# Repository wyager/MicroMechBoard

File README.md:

# MicroMechBoard
This project is the teensy code for Will Yager's custom mechanical keyboard
project. ([blog post](http://yager.io/keyboard/keyboard.html))

The code serves two functions:

1. If plugged into USB, the device will act as a stand-alone keyboard with 33
keys. ("The master")
2. If a second device is plugged into that first device, the two devices will
share relevant information over I2C. In this way, two of these devices can be
connected to form a 66-key keyboard. With some modification to the firmware and
the I2C pull-up resistors, one could theoretically chain up to 129 boards
together (I believe).

## Building/installing
1. Install `avr-gcc`.
2. Install Teensy loader.
3. `cd src`
4. `make`
5. Drag `main.hex` into Teensy loader.
6. Program Teensy.

## Modifying key layout
1. Modify `keys[]` in `KeyMapper.cpp`.
2. Replace values like `KEY_A` with other values from `keylayouts.h`.

This should be fairly simple to figure out. Within the file, I have `keys[]`
laid out just like the physical keys.

## Program structure

### main.cpp

```
       Start USB/I2C
       Determine master/slave status
       
       forever:
              led_status
              => get hardware state from HardwareController
              => debounce buttons with ButtonDebouncer
              => detect changes in buttons with ButtonDeltaDetector
              => map button changes to key changes with KeyMapper
              =: key_changes

              led_status
              => update the slave (if it exists) with the SlaveNotifier
              =: slave_key_changes

              key_changes, slave_key_changes
              => notify the master (over USB or I2C) of key changes with the MasterNotifier
              =: led_status

```

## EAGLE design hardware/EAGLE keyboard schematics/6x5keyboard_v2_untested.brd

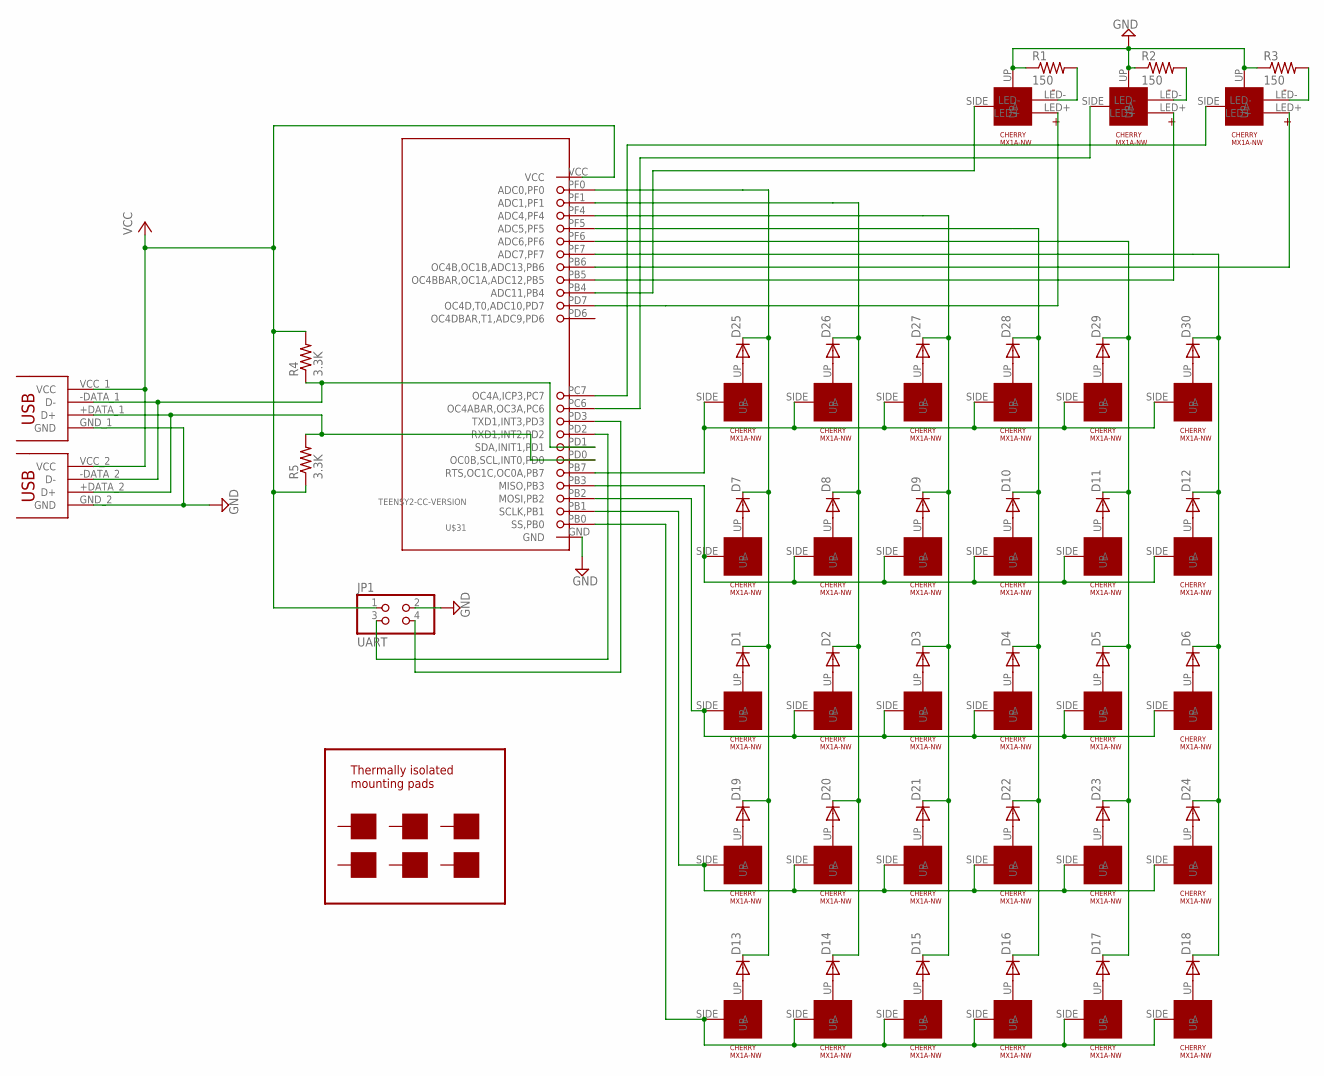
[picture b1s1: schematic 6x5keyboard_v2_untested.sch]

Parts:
D1, D2, D3, D4, D5, D6, D7, D8, D9, D10, D11, D12, D13, D14, D15, D16, D17, D18, D19, D20, D21, D22, D23, D24, D25, D26, D27, D28, D29, D30: 1N4148DO35-7; DO35-7
JP1: UART; 2X02
R1, R2, R3: 150; 0207/10
R4, R5: 3.3K; 0207/10
U$1, U$2, U$3, U$4, U$5, U$6, U$7, U$8, U$9, U$10, U$11, U$12, U$13, U$14, U$15, U$16, U$17, U$18, U$19, U$20, U$21, U$22, U$23, U$24, U$25, U$26, U$27, U$28, U$29, U$30: CHERRY-MX1A-E1NW; CHERRYMX-NN
U$31: TEENSY2-CC-VERSION; TEENSY2
U$32, U$33, U$34: CHERRY-MX1A-E1NW-LED; CHERRYMX-NN-LED
U$35: DUAL-USB-A
U$36, U$37, U$38, U$39, U$40, U$41: MOUNTING-PAD

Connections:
GND: JP1.2, R1.1, R2.1, R3.1, U$31.GND, U$32.UP, U$33.UP, U$34.UP, U$35.GND_1 (GND), U$35.GND_2 (GND)
unnamed: D1.A, U$2.UP
unnamed: D2.A, U$1.UP
unnamed: D3.A, U$3.UP
unnamed: D4.A, U$4.UP
unnamed: D5.A, U$5.UP
unnamed: D6.A, U$6.UP
unnamed: D7.A, U$7.UP
unnamed: D8.A, U$8.UP
unnamed: D9.A, U$9.UP
unnamed: D10.A, U$10.UP
unnamed: D11.A, U$11.UP
unnamed: D12.A, U$12.UP
unnamed: D13.A, U$13.UP
unnamed: D14.A, U$14.UP
unnamed: D15.A, U$15.UP
unnamed: D16.A, U$16.UP
unnamed: D17.A, U$17.UP
unnamed: D18.A, U$18.UP
unnamed: D19.A, U$19.UP
unnamed: D20.A, U$20.UP
unnamed: D21.A, U$21.UP
unnamed: D22.A, U$22.UP
unnamed: D23.A, U$23.UP
unnamed: D24.A, U$24.UP
unnamed: D25.A, U$25.UP
unnamed: D26.A, U$26.UP
unnamed: D27.A, U$27.UP
unnamed: D28.A, U$28.UP
unnamed: D29.A, U$29.UP
unnamed: D30.A, U$30.UP
unnamed: D1.C, D7.C, D13.C, D19.C, D25.C, U$31.PF0 (ADC0,PF0)
unnamed: D2.C, D8.C, D14.C, D20.C, D26.C, U$31.PF1 (ADC1,PF1)
unnamed: D3.C, D9.C, D15.C, D21.C, D27.C, U$31.PF4 (ADC4,PF4)
unnamed: D4.C, D10.C, D16.C, D22.C, D28.C, U$31.PF5 (ADC5,PF5)
unnamed: D5.C, D11.C, D17.C, D23.C, D29.C, U$31.PF6 (ADC6,PF6)
unnamed: D6.C, D12.C, D18.C, D24.C, D30.C, U$31.PF7 (ADC7,PF7)
unnamed: U$19.SIDE (A), U$20.SIDE (A), U$21.SIDE (A), U$22.SIDE (A), U$23.SIDE (A), U$24.SIDE (A), U$31.PB1 (SCLK,PB1)
unnamed: U$1.SIDE (A), U$2.SIDE (A), U$3.SIDE (A), U$4.SIDE (A), U$5.SIDE (A), U$6.SIDE (A), U$31.PB2 (MOSI,PB2)
unnamed: U$7.SIDE (A), U$8.SIDE (A), U$9.SIDE (A), U$10.SIDE (A), U$11.SIDE (A), U$12.SIDE (A), U$31.PB3 (MISO,PB3)
unnamed: U$25.SIDE (A), U$26.SIDE (A), U$27.SIDE (A), U$28.SIDE (A), U$29.SIDE (A), U$30.SIDE (A), U$31.PB7 (RTS,OC1C,OC0A,PB7)
unnamed: U$13.SIDE (A), U$14.SIDE (A), U$15.SIDE (A), U$16.SIDE (A), U$17.SIDE (A), U$18.SIDE (A), U$31.PB0 (SS,PB0)
unnamed: R1.2, U$32.LED-
unnamed: R2.2, U$33.LED-
unnamed: R3.2, U$34.LED-
unnamed: JP1.3, U$31.PD2 (RXD1,INT2,PD2)
unnamed: U$31.PB5 (OC4BBAR,OC1A,ADC12,PB5), U$33.LED+
unnamed: U$31.PB6 (OC4B,OC1B,ADC13,PB6), U$34.LED+
unnamed: U$31.PB4 (ADC11,PB4), U$32.SIDE (A)
unnamed: U$31.PC6 (OC4ABAR,OC3A,PC6), U$33.SIDE (A)
unnamed: U$31.PC7 (OC4A,ICP3,PC7), U$34.SIDE (A)
unnamed: U$31.PD7 (OC4D,T0,ADC10,PD7), U$32.LED+
unnamed: JP1.4, U$31.PD3 (TXD1,INT3,PD3)
unnamed: R4.1, U$31.PD1 (SDA,INIT1,PD1), U$35.-DATA_1 (D-), U$35.-DATA_2 (D-)
unnamed: R5.2, U$31.PD0 (OC0B,SCL,INT0,PD0), U$35.+DATA_1 (D+), U$35.+DATA_2 (D+)
VCC: JP1.1, R4.2, R5.1, U$31.VCC, U$35.VCC_1 (VCC), U$35.VCC_2 (VCC)

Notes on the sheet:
Thermally isolated mounting pads

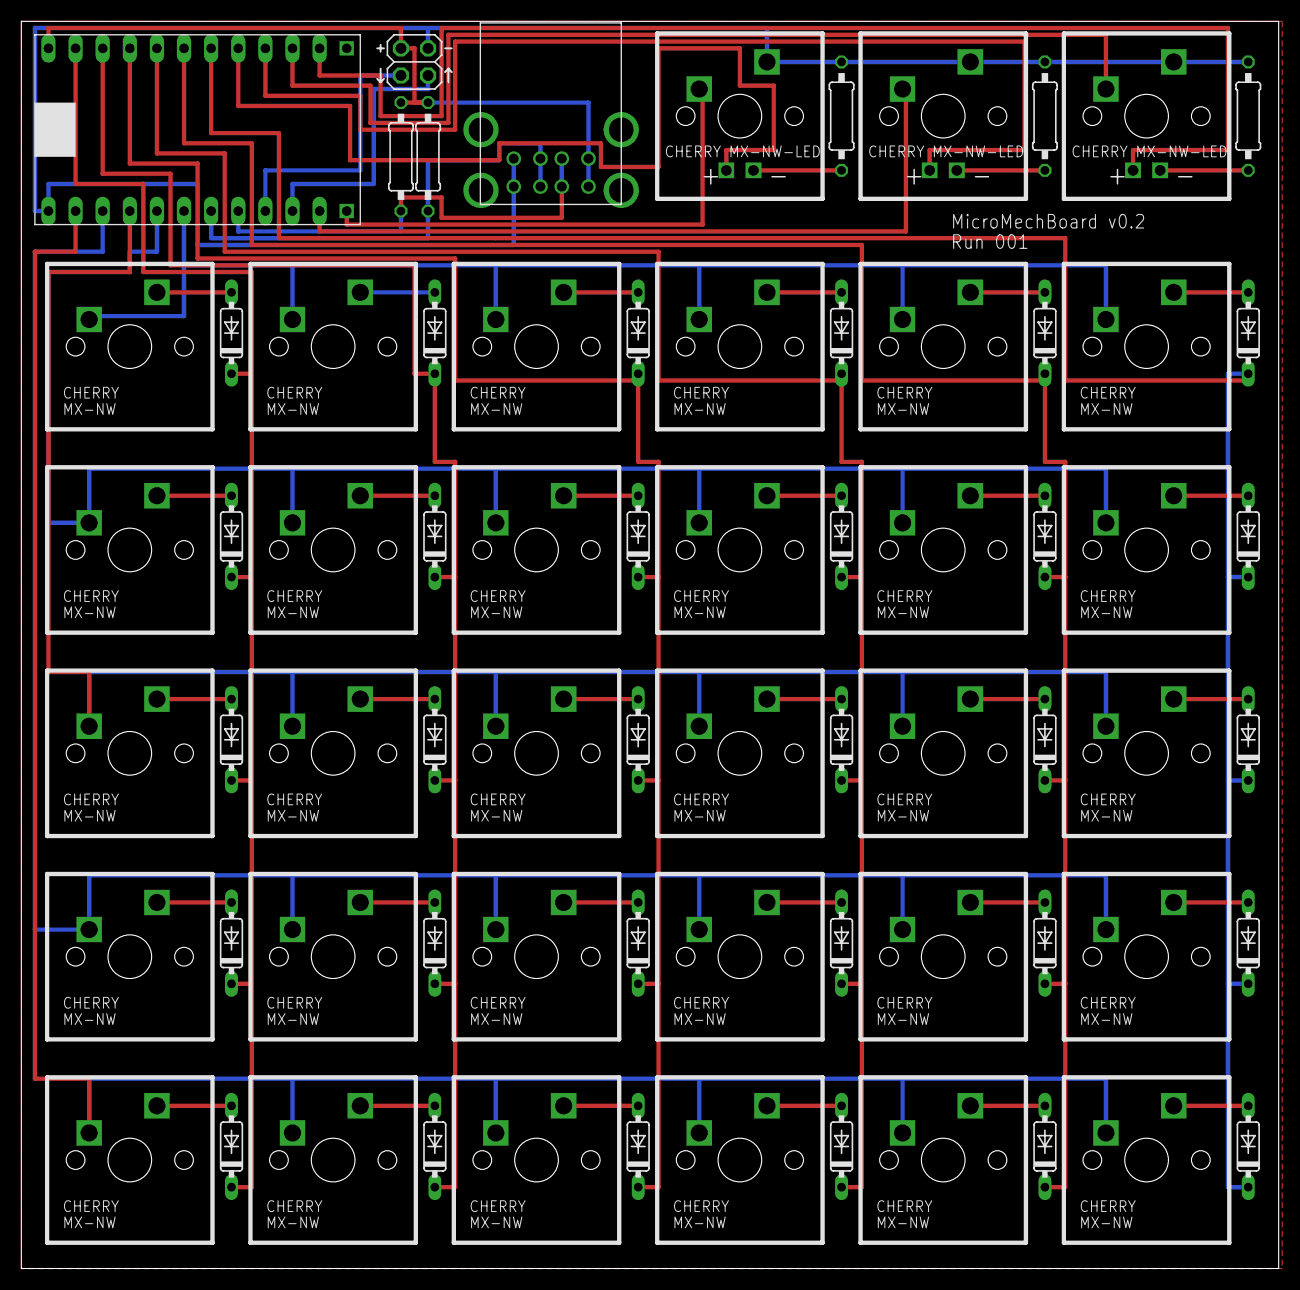
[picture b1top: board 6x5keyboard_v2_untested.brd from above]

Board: 2 copper layers, 117.8 x 116.8 mm, 77 parts (0 on the bottom side), 56 nets.

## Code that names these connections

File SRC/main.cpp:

//
//  main.cpp
//  TeensyRNG
//
//  Created by Will Yager on 6/25/13.
//  Copyright (c) 2013 Will Yager. All rights reserved.
//

extern "C"{
#include <avr/io.h>
#include <avr/pgmspace.h>
#include <stdint.h>
#include <util/delay.h>
#include "usb_keyboard.h"
#include "twi.h"
}
#include <inttypes.h>
#include "KeyboardController.h"

#define CPU_PRESCALE(n) (CLKPR = 0x80, CLKPR = (n))

void send_str(const char *s);


volatile bool i2c_master_has_been_found = false;

//I think this is necessary, since we can't pass an argument to the interrupt handlers
//And we only create the KeyboardController after doing some other stuff
KeyboardController* keyboard_pointer;

//Called when the master sends us some data
//The master sends us data either to A)inform us that we are to be a slave
//or B)inform us of data coming from the host (like the state of various
//LEDs (cap lock etc.) that we can choose to act on.
void interrupt_hander_to_read_i2c_message_from_master(uint8_t* buf,int numBytes){
    if(!numBytes) return;
    
    if(buf[0] == 'S'){//If this is a valid init packet from the master
        i2c_master_has_been_found = true;
    }
    else if(buf[0] == 'L' && numBytes >= 2){//LED status update
        if(keyboard_pointer){//Make sure this pointer is set!
            unsigned char led_status = buf[1];
            keyboard_pointer->computer_interface.set_led_status(led_status);
        }
    }
}



//Called when the master asks for some data (i.e. keyboard status)
void interrupt_handler_to_respond_to_request_from_I2C_master(void){
    if(!keyboard_pointer){//I hope this never happens
        return;
    }

    uint8_t tx_buffer[16];
    
    //Grab the most recent recorded key events (if any) and send them over I2C
    uint8_t num_events = keyboard_pointer->computer_interface.num_saved_key_events;
    
    tx_buffer[0] = num_events;
    
    for (uint8_t event_number = 0; event_number < num_events; event_number++) {
        key_event event = keyboard_pointer->computer_interface.key_events[event_number];
        tx_buffer[event_number*3+1] = event.key & 0xFF;
        tx_buffer[event_number*3+2] = (event.key >> 8) & 0xFF;
        tx_buffer[event_number*3+3] = event.state;
    }
    
    keyboard_pointer->computer_interface.num_saved_key_events = 0;
    
    uint8_t bytes_used = 1+num_events*3;
    
    for (uint8_t i = bytes_used; i<16; i++) {
        tx_buffer[i]=0;
    }

    twi_transmit(tx_buffer, 16);//returns 1 on too long, 2 on not slave, 0 success
    
    //Refresh key status
    keyboard_pointer->update();
}



int main(void)
{
	// set for 16 MHz clock
	CPU_PRESCALE(0);
    //Do NOT use Teensy's LED, as PD6 is currently used for
    //measuring a key and will burn out on key press if
    //the LED is turned on
    
    //Columns (0 to 5, left to right):
    //   PORTF: 0, 1, 4, 5, 6, 7
    DDRF = 0;
    PORTF = 0;
    
    //Rows (0 to 4, bottom to top):
    //    PORTB: 7, 3, 2, 1, 0
    DDRB = 0;//Rows
    PORTB = 0;
    
    //Key 1: PB4
    PORTB |= 1 << 4;//Enable pullup resistor for key 1
    //Key 2: PD6
    PORTD |= 1 << 6;//Enable pullup resistor for key 2
    //Key 3: PC7
    PORTC |= 1 << 7;//Enable pullup resistor for key 3
    //LED 1: PD7
    DDRD |= 1 << 7;//Enable output mode for PD7
    PORTD |= 1 << 7; //Turn on LED 1
    //LED 2: PB5
    DDRB |= 1 << 5;//Enable output mode for PB5
    PORTB |= 1 << 5; //Turn on LED 2
    //LED 3: PB6
    DDRB |= 1 << 6;//Enable output mode for PB6
    PORTB |= 1 << 6; //Turn on LED 3
    
    //Turn on I2C internal pullups. Not really necessary, since we have external pullups too
    PORTD |= (1<<0) | (1<<1);
    

	usb_init();//Turn on USB hardware
    
    twi_setAddress(SLAVE_KEYBOARD_ADDR);//Turn on I2C device as a slave board
    twi_attachSlaveTxEvent(interrupt_handler_to_respond_to_request_from_I2C_master);
    twi_attachSlaveRxEvent(interrupt_hander_to_read_i2c_message_from_master);
    twi_init();
    
    
    //wait until:
    //   USB connects successfully (we are the master board)
    //   OR
    //   We get an init packet over I2C (we are the slave board)
	while (!(usb_configured() || i2c_master_has_been_found)){}


    bool is_master = usb_configured();//If we successfully configured USB, we are the master
    //Otherwise, we are the slave

    KeyboardController keyboard(is_master); //Create a keyboard controller object that deals with
    //A)Scanning physical keys and resolving them to USB codes (via KeyboardHardwareInterface)
    //B)Asking the slave if it has any key-related updates (it handles this internally)
    //    (But only if this board is running as a master board)
    //C)Using KeyboardComputerInterface to either:
    //    C1)Notify the computer of key presses via USB (if master board)
    //    C2)Notify the master board of key presses via I2C (if slave board)
    if(!is_master){//We are a slave. Prepare for slavery
        //Disable USB hardware to save power
        UDCON = 1<<DETACH; //Detach data pins
        USBCON = 1<<FRZCLK; //disable USB controller
        PLLCSR &= ~(1<<PLLE); //disable PLL
        UHWCON &= ~(1<<UVREGE);//Disable USB power regulator

        //Tell the interrupt handler where to look for stored keypress data
        keyboard_pointer = &keyboard;

    }
    if(is_master){//We are a master. Prepare for mastery
        twi_setAddress(0);
    }
    
	_delay_ms(1000);
	
	while (1) {
		if(is_master){
            //////Super duper ultra mega master function/////
            /////Does all the main keyboard-related stuff////
            keyboard.update();
            //////////If we're the master, update()//////////
            ////////////polls the slave over I2C/////////////
            /////////////////////////////////////////////////
        }
        //You may be wondering: If we're not a master, do we ever do anything?
        //The answer, young grasshopper, is yes. However, all actions are initiated
        //by the master over I2C. See interupt handlers defined above
	}
}

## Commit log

2013-08-19 Initial commit
    First upload for all keyboard-related files
2013-08-20 Re-organized and simplified
    Used bools where I should be (but was using chars previously).
    Simplified overall code. There is a new opportunity for a bug to pop up
    in the future (see the new use of the "button_report" type), but it
    would be very difficult to trigger. It basically involves triggering
    more than 8 keys in the same millisecond, and even then isn't
    guaranteed to do anything bad.
2013-08-20 Added some keys
    For some reason, not even close to all of the USB keys are in
    kelayouts.h. Added a few and used them. Also fixed some numbering
2013-08-20 Added to todo
2013-08-20 Added info about key codes
2013-08-20 CC licenses are not for software. Switched to noncommercial MAME license instead.
2013-08-20 Moved SRC/ to src/ for consistency.
2013-08-20 Corrected permissions.
2013-08-20 Moved README to proper location.
2013-08-20 Formatted README with Markdown.
2013-08-20 Fixed minor formatting issue.
2013-08-20 Another small formatting fix.
2013-08-20 Formatted TODO with Markdown.
2013-08-20 Task lists don't work in this file. Removing them.
2013-08-20 Added gitignore, modified parts list file format
    Ignoring OS X DS_Store files
2013-08-20 Added pictures
    Some people have requested clarification on how the circuit should
    look, so I am including a few pictures here.
2013-09-02 Added PWM support
    Added PWM for each LED and replaced the boolean set_led functions with
    wrappers for the PWM set functions.
2013-10-20 Much cleaner design
    Replaced just about everything. The design is now much cleaner and more
    functional (in the language sense). It may be a bit slower, but if it
    is, it's not by much. It is also much cleaner, easier to understand,
    and easier to modify.
2013-11-21 Updated parts list
2013-12-14 Fixed readme
2013-12-14 All done
2013-12-27 Put stuff in folders
2014-01-14 fixed orange light
    No more orange light on teensy. Also initialized led_status.
2014-02-16 Added new, improved, untested keyboard schematic
2014-03-05 Added comment
2014-03-13 Removed some vias
2014-03-13 Removed remaining vias :)
2014-03-13 Re-arranged some vias
    straightened a few things out
2014-03-14 Added dual-Stacked USB-A connector
2014-03-15 Replaced TRRS connector with dual USB-A connector
    Added dual USB-A connector to allow for better daisy-chaining support
    (including possible support for hot-swapping). Thanks to CaitSith2 for
    assistance.
2014-03-15 Tidied up the schematic.
2014-03-15 Corrected the ERC warnings.
2014-03-15 Deleted part values. They may not apply for all situations.
2014-03-15 Updated license
2014-03-16 Board routed with groovy looking traces, using freerouting.net
2014-03-17 Clarified comment
2014-03-18 Changed all rectangles into proper SMD pads.
2014-03-18 7x6 Keyboard layout
2014-03-18 Groovy traces now in their own files. 6x5keyboard_v2_untested.* is exclusively right-angle traces now.
2014-03-18 Replaced rectangles with actual library based mounting pads.
2014-03-18 Moved schematics
2014-04-23 Fixed oversensitivity of upper buttons
2014-07-19 Updated comments
2014-07-20 Updated some private fields and constructors
2014-08-29 Trying to fix bug with some compilers
2016-01-21 Added website link
